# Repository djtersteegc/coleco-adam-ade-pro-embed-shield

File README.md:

# Coleco Adam ADE Pro Mini OLED Edition

Yet another version of hardware compatible with the [AdamNet Drive Emulator](https://github.com/Kalidomra/AdamNet-Drive-Emulator) (ADE) software by Sean Myers. This is a smaller version of my [previous design](https://github.com/djtersteegc/coleco-adam-ade-pro-shield) now built around an (unofficial) Aruduino Mega 2560 PRO Embed board and replacing the 1602 LCD with an 0.91" I2C OLED screen and SMD components.

Here's a size comparison between the two versions.

All components can be sourced from the usual low cost China based vendors for a total build cost of around $20.  Please see the hardware component page for more details.

[Hardware Component Choices](https://djtersteegc.github.io/coleco-adam-ade-pro-embed-shield/components.html)

An interactive BOM and parts placement diagram is also available.

[Interactive Bill of Materials (BOM)](https://djtersteegc.github.io/coleco-adam-ade-pro-embed-shield/ibom.html)

# Assembley

Even though this is mostly SMD, assembley is pretty easy since everything is 0805 sized or bigger, but you do need to follow a certain order since some components overlap each other or become difficult to reach. Start by doing all the SMD components (resistors, caps, IC, transistor, and SD card socket) on the underside of the board. I used solder paste and hot air, but you could also hand solder these. Pay attention to the orientaion of the two polarized caps if you elect to install them.

Then flip the boad over and install the switches.  For this I used solder paste and a hand iron.

Next install the RJ12 jack.

I soldered the headers on next, but you could also the do the OLED and LED if you don't want to seperate the boards again after soldering the headers on.  I tend to do the OLED last just to minimize the chance of breaking it.  For the LED I placed the top half of the board in the case and used a 1mm spacer under the case top of get a nice reveal and then soldered it in. For the OLED I installed in on 3mm thick double sided foam tape and then soldered the headers on once I confirmed it was straight.  

For the headers I like to screw in the two 14.6mm spacers and assemble the two halves to make sure everything stays aligned.  Use M2.5x6mm (or longer) screws for the spacers.  The one with the cut on the top goes in the hole by the SD card with the cut out area facing the SD card socket.

After everything is soldered I then inserted four of the 3.6mm header block spacers in all four corners to ensure everything stayed leveled and the male header pin aren't pushed to far into the female headers.

# Programming

This version does require updates to Sean's original ADE code base to support the OLED screen and remaps a number of pins to support this PCB layout.   I have a fork of his repo [here](https://github.com/djtersteegc/AdamNet-Drive-Emulator), and there is a precompiled ADE-Pro-Mini-OLED_v0.92.hex binary if you just want to upload via something like AVRDude.

If you decided to build it yourself, make sure 

`#define PRO_MINI_OLED_BOARD`

is uncommented in AdamNet_Drive_Emulator.ino.  I used the u8x8 library for the OLED screen, but even with hardware I2C, the refresh rate is still much slower than the old 1602 LCD.  You don't notice it when viewing the screen, but it was enough to throw off the AdamNET timing when dumping debug info to the screen so that functionality has been disabled in this version (debug messages still are sent over the serial port).

# Debugging and Power

Power comes directly from the AdamNET connector and there are no onboard jumpers or diodes to prevent backfeeding if you also plug in the Arduino while  connected to the Adam.  That's why there is no cutout in the cover for the USB connector.  If you do need to connect the USB port for serial debugging, you can create an AdamNET RJ12 cable with the 5V line (pin 6 on the ADE side) disconnected.

# Case

STL's and the [DesignSpark Mechanical](https://www.rs-online.com/designspark/mechanical-software) source file for a 3D printable enclosure and the various standoff and spacers are in the **case** directory. Make sure to print seven copies of the button file and four copies of the 3.6mm spacer.

There are two versions of the lid file, one that covers the UBS port (the one most people should use), and one that exposes it for development purposes.  Read the warining about powering via USB above!  The lid is snap fit, but the is also a provision to screw it into the bottom of one of the spacers using a m2.5x15mm (or longer) scew.

# Getting a Board

If I have extra PCB's, they will be listed on Tindie (soon...).

Otherwise you can download the Gerbers and use your favorite fab (JLCPCB, PCBWay, etc.) to make your own batch.  It's a standard two layer, 1oz copper board with dimensions of 56mm x 38mm.

# Hardware Revisions

### Version 1.0

Tested and working.

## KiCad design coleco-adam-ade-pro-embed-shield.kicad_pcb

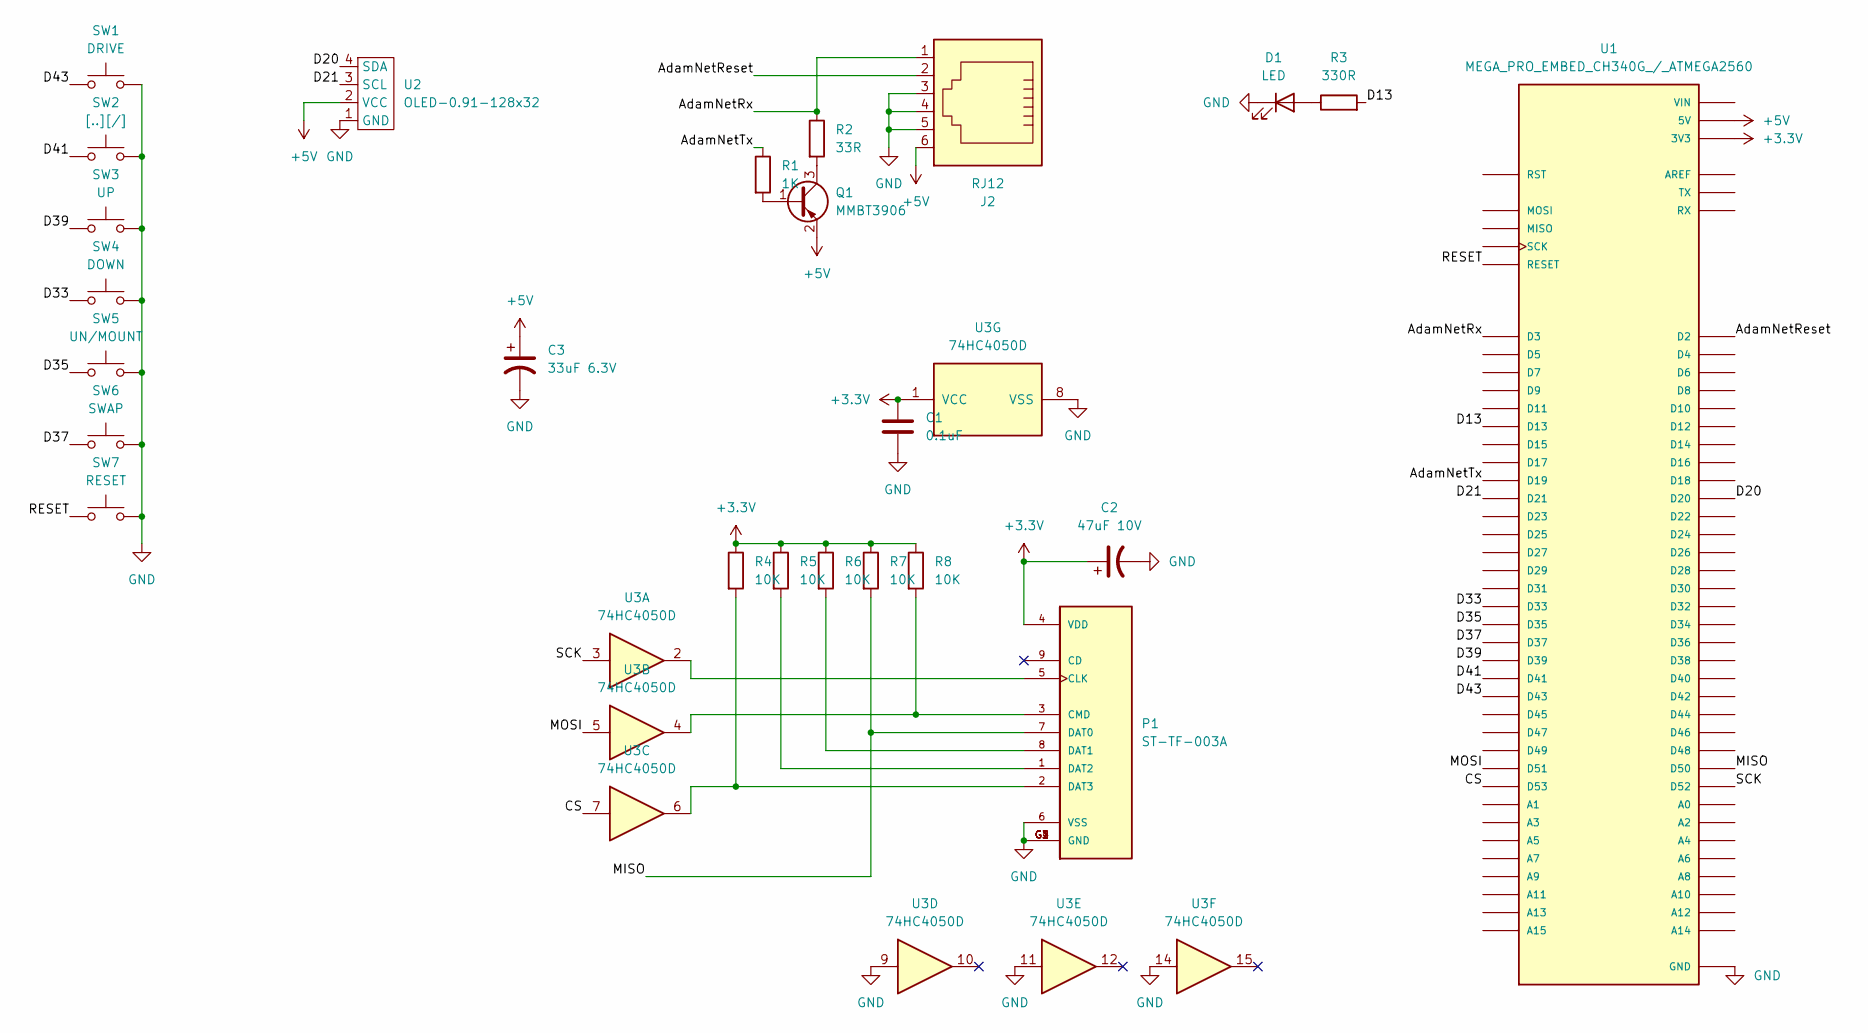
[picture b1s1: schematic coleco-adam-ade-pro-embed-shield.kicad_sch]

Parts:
C1: 0.1uF; C_0805_2012Metric_Pad1.18x1.45mm_HandSolder
C2: 47uF 10V; CP_EIA-3528-21_Kemet-B_Pad1.50x2.35mm_HandSolder
C3: 33uF 6.3V; CP_Elec_5x5.8
D1: LED; LED_D3.0mm
J2: RJ12; RJ12_Amphenol_54601
P1: ST-TF-003A; SUNTECH_ST-TF-003A
Q1: MMBT3906; SOT-23
R1: 1K; R_0805_2012Metric_Pad1.20x1.40mm_HandSolder
R2: 33R; R_0805_2012Metric_Pad1.20x1.40mm_HandSolder
R3: 330R; R_0805_2012Metric_Pad1.20x1.40mm_HandSolder
R4, R5, R6, R7, R8: 10K; R_0805_2012Metric_Pad1.20x1.40mm_HandSolder
SW1: DRIVE; SW_Push_SPST_NO_Alps_SKRK
SW2: [..][/]; SW_Push_SPST_NO_Alps_SKRK
SW3: UP; SW_Push_SPST_NO_Alps_SKRK
SW4: DOWN; SW_Push_SPST_NO_Alps_SKRK
SW5: UN/MOUNT; SW_Push_SPST_NO_Alps_SKRK
SW6: SWAP; SW_Push_SPST_NO_Alps_SKRK
SW7: RESET; SW_Push_SPST_NO_Alps_SKRK
U1: MEGA_PRO_EMBED_CH340G_/_ATMEGA2560; MODULE_MEGA_PRO_EMBED_CH340G___ATMEGA2560; PARTREV 12/May/2017
U2: OLED-0.91-128x32
U3: 74HC4050D; SOIC-16_3.9x9.9mm_P1.27mm

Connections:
+3.3V: C1.2, C2.1, P1.4 (VDD), R4.1, R5.1, R6.1, R7.1, R8.1, U1.3V3_1 (3V3), U1.3V3_2 (3V3), U3.1 (VCC)
+5V: C3.1, J2.6, Q1.2 (E), U1.5V_1 (5V), U1.5V_2 (5V), U1.5V_3 (5V), U2.2 (VCC)
/AdamNetReset: J2.2, U1.D2
/AdamNetRx: J2.1, R2.1, U1.D3
/AdamNetTx: R1.1, U1.D19
/CS: U1.D53, U3.7
/D13: R3.2, U1.D13
/D20: U1.D20, U2.4 (SDA)
/D21: U1.D21, U2.3 (SCL)
/D33: SW4.1, U1.D33
/D35: SW5.1, U1.D35
/D37: SW6.1, U1.D37
/D39: SW3.1, U1.D39
/D41: SW2.1, U1.D41
/D43: SW1.1, U1.D43
/MISO: P1.7 (DAT0), R7.2, U1.D50
/MOSI: U1.D51, U3.5
/RESET: SW7.1, U1.RESET
/SCK: U1.D52, U3.3
GND: C1.1, C2.2, C3.2, D1.1 (K), J2.3, J2.4, J2.5, P1.6 (VSS), P1.G1 (GND), P1.G2 (GND), P1.G3 (GND), P1.G4 (GND), SW1.2, SW2.2, SW3.2, SW4.2, SW5.2, SW6.2, SW7.2, U1.GND_1 (GND), U1.GND_2 (GND), U1.GND_3 (GND), U2.1 (GND), U3.8 (VSS), U3.9, U3.11, U3.14
unnamed: D1.2 (A), R3.1
unnamed: P1.1 (DAT2), R5.2
unnamed: P1.2 (DAT3), R4.2, U3.6
unnamed: P1.3 (CMD), R8.2, U3.4
unnamed: P1.5 (CLK), U3.2
unnamed: P1.8 (DAT1), R6.2
unnamed: Q1.1 (B), R1.2
unnamed: Q1.3 (C), R2.2
unnamed: U1.VIN_1 (VIN), U1.VIN_2 (VIN)

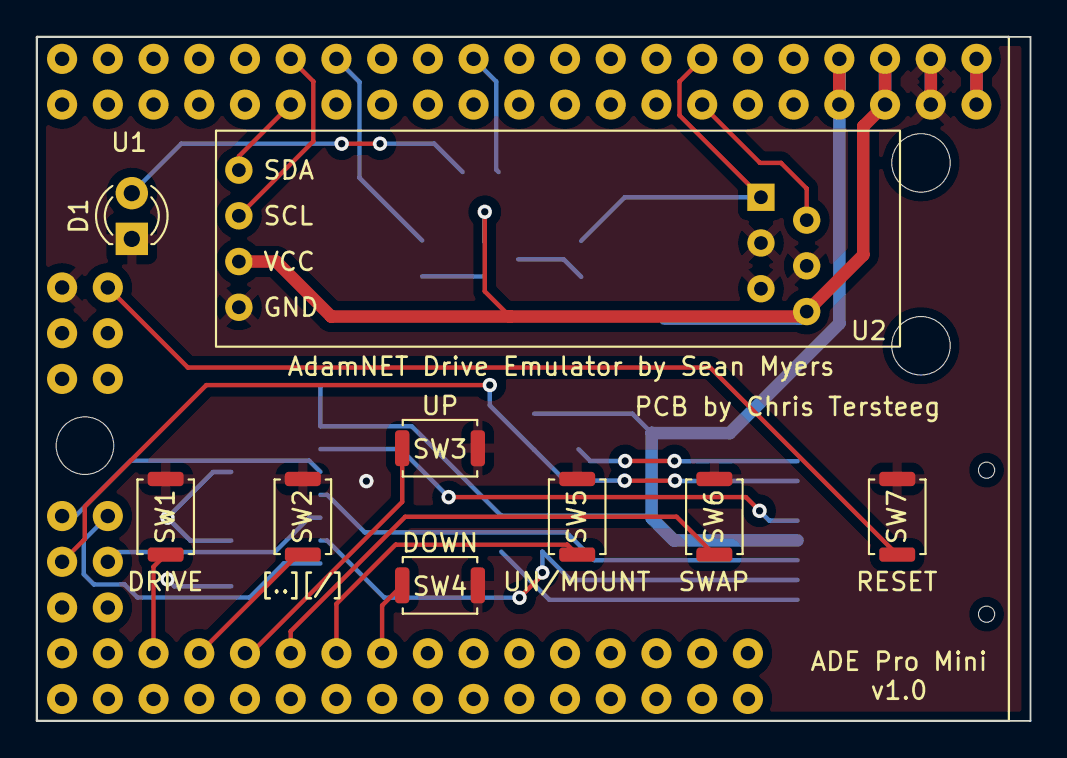
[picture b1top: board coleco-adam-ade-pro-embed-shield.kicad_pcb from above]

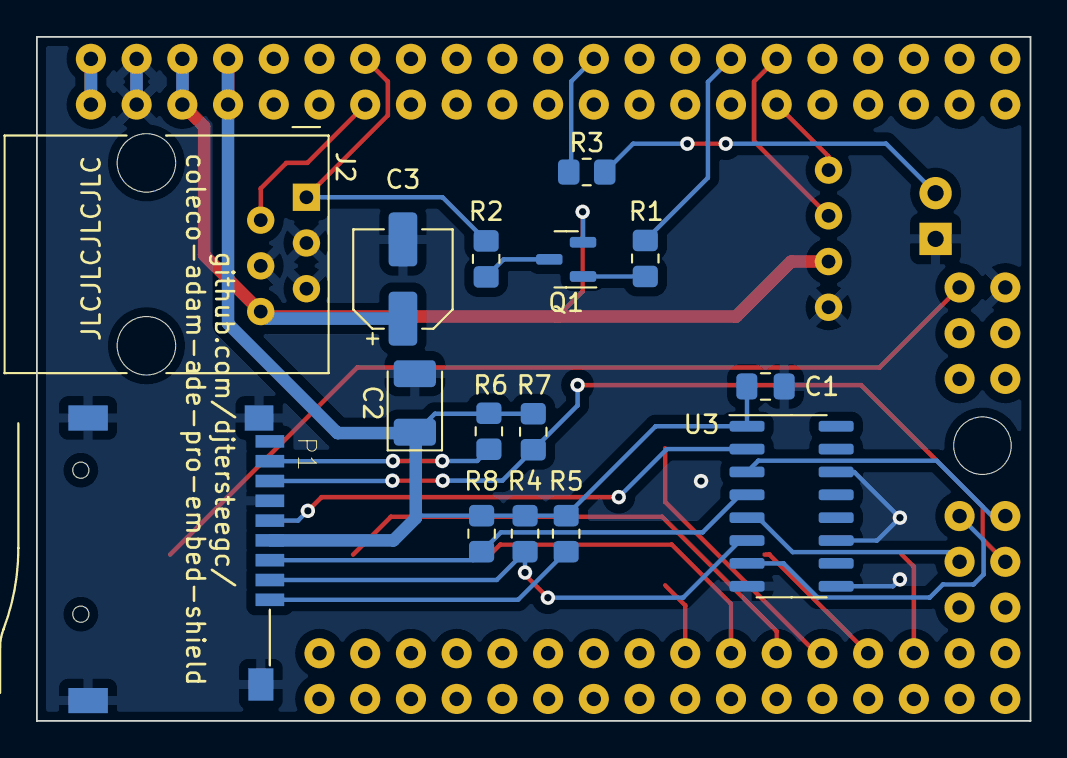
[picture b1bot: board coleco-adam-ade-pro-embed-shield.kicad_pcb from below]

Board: 2 copper layers, 55.2 x 38.0 mm, 25 parts (15 on the bottom side), 29 nets.

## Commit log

2023-01-08 Initial version
